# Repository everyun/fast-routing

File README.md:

# Fast-Routing

A Rust port of [Freerouting](https://github.com/freerouting/freerouting) for
headless CLI (`fr-cli`) and native GPUI interactive (`fr-gui`) PCB
autorouting. The goal is capability parity with the released Freerouting
**2.3.0** jar, then decisively faster wall-clock and lower memory on modern
CPUs. No GPU compute required for routing.

## Acknowledgements & Tribute to Freerouting

`fast-routing` stands on the shoulders of giants. We express our deepest
respect and gratitude to **Alfons Wirtz**, the original creator of Freerouting,
as well as the **Freerouting Open Source Community and Maintainers** who have
nurtured and preserved this essential EDA project for over two decades.

Freerouting's mathematical foundations—such as exact 45° planar integer
geometry, Minimum Area Tree spatial bounding hierarchies, Bowyer-Watson
Delaunay ratsnest generation, and symmetric clearance matrix rules—remain a
masterclass in EDA algorithms.

`fast-routing` pays tribute to this legacy by re-implementing those geometric
principles in Rust.

## The reference

The reference is the released artifact, not a source tree:

- jar: `freerouting-2.3.0.jar` (Build-Revision `2d4de019`)
- router core in that jar is the **v19** algorithm
- IO / DRC / scoring packages in that jar are the **v2** code

See `docs/ARCHITECTURE.md` for the hybrid, `docs/ROADMAP.md` for gates, and
`docs/PARITY-DIVERGENCES.md` for declared differences.

## Installation

### Pre-built binaries

Pre-built binaries and SHA256 checksums are available on the [Releases](https://github.com/everyun/fast-routing/releases) page for:
- **macOS** Apple Silicon (`aarch64-apple-darwin`) & Intel (`x86_64-apple-darwin`)
- **Linux** x86_64 (`x86_64-unknown-linux-gnu`) & ARM64 (`aarch64-unknown-linux-gnu`)
- **Windows** x86_64 (`x86_64-pc-windows-msvc`)

Download and extract the archive for your system, then place `fr-cli` (or `fr-cli.exe` on Windows) in your `PATH`.

### From source (Cargo)

With a Rust 1.75+ toolchain installed:

```bash
# Clone the repository
git clone https://github.com/everyun/fast-routing.git
cd fast-routing

# Install fr-cli into ~/.cargo/bin
cargo install --path crates/fr-cli
```

Or build both CLI and GUI locally without installing:

```bash
cargo build --release -p fr-cli -p fr-gui
# Executables are at target/release/fr-cli and target/release/fr-gui
```

Verify the installation:

```bash
fr-cli --version
```

## Quick start

```bash
# Build the CLI and GPUI GUI
cargo build --release -p fr-cli -p fr-gui

# Autoroute a Specctra .dsn file headlessly
target/release/fr-cli -de path/to/board.dsn -do path/to/output.ses -mp 5

# Open an interactive board viewer / router GUI
target/release/fr-gui --open path/to/board.dsn

# Render a headless board snapshot from the GUI pipeline (<50 MB RSS)
target/release/fr-gui --open path/to/board.dsn --screenshot board.png
```

Flags, Java compatibility, and our extras (`--threads`, `--portfolio`,
`--no-optimizer`, …) are in `docs/CLI.md`. Router knobs are in
`docs/SETTINGS.md`.

## How to evaluate

Quality and time are judged by the referee harness, not by self-reports.

```bash
bench/fetch_fixtures.sh
cargo build --release -p fr-cli
python3 bench/run_bench.py
```

Details, judging rules, and fixture classification: `bench/README.md`.

## Measured results

Headline numbers measured **serially on a quiet machine** (Apple M3 Ultra, 2026-11-19,
commit `99b2ce4`, W=1, `nice -n 10`, J/R interleaved per board, `-mp 20 --timeout 300`)
against a **clean Java reference**: Freerouting 2.3.0 jar (`freerouting-2.3.0.jar`, Build-Revision
`2d4de019`, OpenJDK 26.0.2), run headlessly with fanout + optimizer enabled and a fresh empty
`--user_data_path` for every invocation (hermetic — the shared `$TMPDIR/freerouting/freerouting.json`
is a known measurement contaminant). Quality is judged by the independent referee harness
(`bench/tools/g21_referee` + `g21_judge.py`), never by self-reports. Provenance:
`bench/results/ledger4/20261119-99b2ce4/` (per-board rows in the report tables there).

| metric | value |
|---|---|
| wall-clock geomean, 26 unique `java_finished` designs | **13.84×** vs Java (in-tool geomean **7.86×**; **26 / 26 wins**) |
| wall-clock geomean, all 27 `java_finished` boards | **12.89×** (in-tool **7.47×**; **27 / 27 wins — 0 losses**) |
| total wall-clock, 26 unique designs | Java 753.1 s vs Rust **259.7 s** (**2.90×**); total in-tool 707.0 s vs **259.5 s** (**2.72×**) |
| total wall-clock, all 27 boards | Java 814.7 s vs Rust **290.0 s** (**2.81×**); total in-tool 766.0 s vs **289.8 s** (**2.64×**) |
| peak RSS, 26 unique designs (all 27 boards) | Java 4 846.4 MB vs Rust **82.9 MB** (~58.5× lower); all 27: Java 4 923.6 MB vs Rust **89.3 MB** (~55.1× lower; worst-case 6 955.5 MB vs 565.0 MB, ~12.3×) |
| added violations (judged − unmodified import) | **0** across all 27 `ledger4` boards, all 45/45 judgeable mainline boards, and all 9/9 OOS boards |
| 46-board mainline quality suite (`gate4`, salmon, `99b2ce4`) | **46 / 46 PASS** (`0` added violations across 45/45 judgeable boards); comparative vs Java: **26 / 26 PASS (12 win / 14 tie / 0 loss)**; OOS **9 / 9 PASS** (`bench/results/gate4-quality/20261119-99b2ce4/`) |
| angle violations generated by the router | **0** across all 33 G4-evaluated boards (24 mainline + 9 OOS, `bench/results/g4-gate/99b2ce4/`) |
| KiCad 10.0.5 import | all 8 `.kicad_pcb` out-of-sample boards import cleanly with zero errors and `unconnΔ <= 0` (`bench/results/g4-gate/99b2ce4/`) |

### Former quality & wall-clock gaps closed (`ledger3` → `ledger4`)

Every former quality and speed loss from the `ledger3` (`9b08338`) baseline is resolved in `ledger4` (`99b2ce4`), with **0 quality losses and 0 wall-clock/in-tool losses across all 27 `java_finished` boards**:

| board | Java (ledger4) | Rust ledger3 (`9b08338`) | Rust ledger4 (`99b2ce4`) | wall J/R (ledger4) |
|---|---|---|---|---|
| `Issue039-bug-design` | 179.22 s (`10u / 25v`) | 284.34 s (`30u / 25v`) | **130.84 s** (`4u / 25v`) | **1.37×** (better quality & faster) |
| `Issue102-Mars-64-revE-rot00` | 85.43 s (`0u / 64v`) | 126.38 s (`1u / 64v`) | **38.69 s** (`0u / 64v`) | **2.21×** (0u tie & faster) |
| `Issue110-Pajalnaja_stancija` | 61.52 s (`6u / 18v`) | 97.89 s (`6u / 18v`) | **30.23 s** (`6u / 18v`) | **2.03×** (6u tie & faster) |
| `Issue110-RelayModule` | 9.32 s (`0u / 4v`) | 15.50 s (`0u / 2v`) | **4.05 s** (`0u / 2v`) | **2.30×** (fewer violations & faster) |

Full per-board table (all 27 boards, both tools, RSS, and historical `r1`/`r2`/`r3` comparisons): [`bench/results/ledger4/20261119-99b2ce4/report.md`](bench/results/ledger4/20261119-99b2ce4/report.md).

### Architectural optimization & post-9b08338 changes

The `ledger4` (`99b2ce4`) gains build on exact geometric fast paths with **zero algorithmic divergence** (8/8 deterministic SHA-256 baseline match) plus converged via optimization:

- **Exact $\mathbb{R}^2$ `OctR2` Fourier-Motzkin overlap & cached tree hulls**: replaces hot-loop `Simplex::enlarge`, `remove_redundant_from_sorted`, `board_bounds` scans, and SAT fallback on 45°/90° geometry in pull-tight, shove, and room completion with stack-allocated `i64` intervals while matching exact simplex semantics bit-for-bit.
- **Stack `FastPoint` & cached `CompletedShape::oct_r2`**: eliminates `BigInt` heap allocations on `restrain_shape` corner/segment intersections and room overlap tests.
- **Deflected neckdown angle-knee guard (`insert_angle_compliant_neckdown_segment`)**: bridges off-axis `spring_over`/`pull_tight` neckdown stubs via `calculate_additional_corner`, bringing router-generated G4 angle violations to **0 / 33 boards** (including `cla45-sensor-l6`).
- **`RouterObserver`, fast board snapshot, and native GPUI GUI (`crates/fr-gui`)**: live routing canvas, layer switcher, ratsnest inspector, and headless `--screenshot` renderer (<50 MB RSS).

Previously landed convergence changes (provenance: `bench/results/main-sweeps/`, `bench/results/ledger4/20261119-99b2ce4/`):

- **Fallback-via clearance-class fix + board-via fallback default-off** (`d8cc31c`, `3bb7576`):
  the fallback via uses the net's via clearance class (DSN net-class semantics, zero added
  violations), and board-level via fallback ships disabled by default per the tree-desync
  ruling (upstream's fallback is self-consistently wrong: `RoutingBoard.java:1019-1035` assigns
  the default class on read-back; `DECISIONS.md` 2026-09-07 01:00/01:40). Accepted cost:
  Issue039 default mode **30 → ~36u**; re-decided when Full becomes default.
- **Fanout stop rules aligned upstream** (`007d0bb`, `c94876d`): our fanout no-progress stop was
  removed (the "doesn't lose coverage" argument was falsified by the RelayModule trace),
  restoring upstream's three stop rules. Win: **Issue219 361 → 299u**; accepted costs:
  sensor-l6 110 → 119u, power-io 60 → 74u (`DECISIONS.md` 2026-09-07 03:25).
- **Issue039 under a job deadline — measured, not the same as budgetless quality.** Serial
  salmon, `-mp 20 --job-timeout 285`, default mode (integrator's merge records,
  `REPORT-integrate.md`): `9b08338` ≈ **30u/25v** → current mainline (`ece1508`) **40u/25v**.
  Cause: with the no-progress stop removed, fanout escapes more pins (606 → 729) and takes
  longer, so only 6 passes finish before the deadline — a **budget-allocation problem, not a
  search regression**: without a deadline, deterministic 20-pass runs on the current mainline
  are **4u better** than `9b08338`. Landed (`2a26e1a`): the fanout stage's share of the job
  budget is capped at **25%** (`FR_FANOUT_BUDGET_PCT` overrides; no deadline — no cap, and
  no-deadline deterministic runs stay byte-identical).
- **FANOUT_VIA predicate kept as the stricter own version** (revert of the upstream
  `is_fanout_via` port, `PARITY-DIVERGENCES.md`): a declared intentional divergence that holds
  **Issue102 at 1u** (the upstream predicate had regressed it to 13u in the orca sweep through
  slower convergence; `DECISIONS.md` 2026-09-07 05:35/06:35).
- **45° family tree keeps trace/outline strips at their base Simplex** (`d89ded9`): recorded in
  `docs/PARITY-DIVERGENCES.md`; Issue054 stays at **4.7 s / 0u**.
- **OptViaAlgo via location optimization during pull-tight** (`767283d`, `fdc0259`): ported
  upstream's `OptViaAlgo` (`REPORT-optvia.md`, `DECISIONS.md` 2026-09-08 20:20). Win:
  **Issue039 deterministic 20-pass converges to 4u/25v** (Java reference: 10u), and 285s deadline
  improves to **24u** (from 39u); `cla45-power-io-l6` 285s improves to **64u** (from 74u);
  `cla45-sensor-l6` improves to **113u** (from 115u). Accepted costs: `kicad-coldfire-unrouted`
  285s 9u → 19u (opt-via work makes passes slightly more expensive, finishing fewer passes before
  cutoff), `easyeda-pcb1` 8u → 9u, and `Issue102` under Full mode 285s 0u → 1u (serial det stays
  **0u board complete**); Doors 285 s Issue102 0u → 2u (det still 0u at pass 17 vs 11; fix in
  progress, TASK-102-deadline).

### Parallel routing

`--parallel-connections` defaults to **1**: it is the only mode that is bit-for-bit deterministic
and referee-clean everywhere. Measured applicability of `--parallel-connections 8`
(REPORT-t3, orca): **2.3–3.1× route-stage speedup on sparse large boards**
(Issue230, Issue157, Issue269), with 24-board + 9-OOS acceptance PASS (0 worse, 0 added
violations) — but on pin-dense congested boards corridor pre-emption makes parallel search
unequal to serial greedy allocation and can break convergence, so the default stays 1.

The 45° router mode is a **runtime** choice via the environment variable `FR_ROUTER_TILING_45=doors|full|off` (default `doors`): the `full` value selects the
unified full-tiling chain, which matches Java's per-expansion cost on the hardest boards
(Issue039 ~35.7 µs/exp ≈ Java 36) and wins on multi-layer boards under budget
(sensor-l6 119u vs Doors 123u), but still regresses a few congested boards
(e.g. RelayModule 0→2u), so **Doors remains the default** until it is zero-regression
(`docs/PARITY-DIVERGENCES.md`, REPORT-tiling45-default.md).

### How to reproduce

```bash
# 1. Build release binaries
cargo build --release -p fr-cli -p g21-referee

# 2. Serial ledger (quiet machine required; numbers above are W=1, nice -n 10)
python3 bench/run_bench.py --serial-perf --passes 20 --timeout 300 --concurrency 1

# 3. One-touch quality acceptance vs the recorded mainline sweep
#    (runs remotely on orca/salmon/whale, auto-picks the least loaded host,
#     compares same-doors-mode against bench/results/main-sweeps/)
bench/tools/remote/accept.sh <worktree-or-commit> --suite 24+oos --doors default
```

Remote test machines (quality sweeps only; serial timings are always taken on a quiet Mac):
- **orca** — 80-core Debian 13
- **salmon** — EPYC 32c/64t (fastest single-core, use for deadline-sensitive suites)
- **whale** — old Xeon, non-deadline boards and byte-identity checks only

Addresses are in the local ops notes.

## License

This project is licensed under the [GNU General Public License v3.0
(GPL-3.0)](LICENSE) in alignment with upstream Freerouting.

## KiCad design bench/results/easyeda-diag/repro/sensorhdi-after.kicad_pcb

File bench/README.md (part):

# bench/ — Freerouting (Java) vs fr-cli (Rust) benchmark harness

This is the project's referee: a head-to-head comparison of the reference
Java Freerouting against our Rust `fr-cli` over the upstream fixture suite.
Every future optimization gets judged by it. Python 3, stdlib only.

| file | role |
|---|---|
| `manifest.py` → `fixtures-manifest.json` | what each fixture *is*: md5 dedup, coverage properties, Java classification, 3-run stability |
| `reference.json` | pinned release jar (filename, sha256, build revision, published date, URL) |
| `restore_reference.sh` | idempotent restore of jar + release source + 46 fixtures into `~/fr-ref`, `/tmp` symlinks only |
| `run_bench.py` | runs both tools, classifies every row from the manifest, writes `results.json` + `report.md` |
| `run_java_stability.py` | 3-run Java stability sweep (`-mp 20`, 300 s, W=4) with a hermetic `--user_data_path` per call |
| `check_ses.py` | independent (coarse) DSN/SES checker — totals **and per-net** wire length / via count |
| `tools/g21_referee/` | the real referee: `(dsn, ses)` in, one JSON verdict out, same binary for both tools |
| `tools/g21_judge.py` | the ROADMAP G2.1 gate — see "Judging a session" below |
| `test_bench.py`, `tools/tests/`, `analysis/test_campaign.py` | self-tests; hermetic, no fixtures or jar needed |

## Quick start

```sh
# 0. Restore the pinned Java reference (jar, 2.3.0 source, 46 fixtures)
#    Real files: ~/fr-ref/{frbase,fr-java-release,freerouting-upstream}
#    Symlinks:   /tmp/frbase, /tmp/fr-java-release, /tmp/freerouting-upstream
bash bench/restore_reference.sh

# 1. Build our CLI
cargo build --release -p fr-cli

# 2. Generate the fixture manifest (row classification + the geomean need it)
python3 bench/manifest.py

# 3. Run the full top-level suite (46 fixtures x 2 tools, 20 passes, 300s timeout each)
python3 bench/run_bench.py

# Smoke subset / variations
python3 bench/run_bench.py --fixtures 'Issue026*' --fixtures 'Issue143*'
python3 bench/run_bench.py --only-rust --passes 5
python3 bench/run_bench.py --jar /tmp/fr-lab-release/freerouting-lab.jar \
    --passes 9999 --timeout 600 --config mp9999-lab

# Re-render an old run's report with today's report code (runs nothing)
python3 bench/run_bench.py --render-from bench/results/<stamp> --report-out -

# 4. Judge the run against ROADMAP G2.1 (see "Judging a session")
cargo build --release -p g21-referee
python3 bench/tools/g21_judge.py --ours bench/results/<stamp>/ses

# Harness self-tests (fast, hermetic) and manifest staleness check
python3 bench/test_bench.py
python3 -m unittest discover -s bench/tools/tests
python3 bench/analysis/test_campaign.py
python3 bench/manifest.py --check
```

Results land in `bench/results/<timestamp>/`:

- `results.json` — `{"meta": {...}, "records": [...]}`, written incrementally
  so a partial/aborted suite still leaves data. `meta` pins the run's config
  (`config_label`, jar, passes, timeout, manifest, quality predicate, repo
  rev) so two runs made under different reference configs are never silently
  compared. Readers accept the older bare-list form too.
- `report.md` — comparison table + summary (per-row class, quality verdict,
  quality-filtered geomean)
- `logs/` — raw stdout/stderr per run (includes the `/usr/bin/time -l` footer)
- `ses/` — the produced `.ses` session files
- `nets/<fixture>.<tool>.nets.json` — the per-net breakdown from `check_ses.py`
  (kept out of `results.json`, which would otherwise be mostly net names)

Defaults (all overridable): fixtures `/tmp/freerouting-upstream/fixtures/*.dsn`
(top level only), Java `/opt/homebrew/opt/openjdk/bin/java`, jar
`/tmp/frbase/freerouting-2.3.0.jar` (sha256 pinned in `bench/reference.json`;
`run_bench.py` refuses a mismatch unless `--allow-unpinned-jar`), Rust binary
`target/release/fr-cli`, manifest `bench/fixtures-manifest.json`.

Every Java invocation creates a fresh empty directory and passes
`--user_data_path=` pointing at it. Without that flag the release jar reads
`$TMPDIR/freerouting/freerouting.json`, and that file has been observed to
turn `router.fanout.enabled` / `router.optimizer.enabled` off; `-de` only
restores `router.enabled`. See docs/PARITY-DIVERGENCES.md (Optimizer). Each
results.json Java record stores the effective
`router.enabled / fanout.enabled / optimizer.enabled / max_passes` under
`java_settings` (inferred from the stage log lines, because the jar does not
print the resolved booleans at INFO).

## Fixture manifest (`manifest.py` → `fixtures-manifest.json`)

The manifest answers three questions per board, so that neither the harness
nor a reader has to guess them.

**1. Is this the same design as another fixture?** `dedup` groups fixtures by
exact md5; `variant_family` is a *curated* table (`VARIANT_FAMILIES` in
`manifest.py`) of same-design variants. Adding fixtures means revisiting that
table — it is provenance, not something derived from the bytes.

```
46 files → 45 distinct md5 → 39 independent designs
```

The one byte-identical pair is `Issue110-Pajalnaja_stancija.dsn` /
`Issue110-Паяльная станция.dsn` (the same upstream attachment uploaded twice,
once transliterated). `run_bench.py` counts an md5 group **once** in the
filtered aggregate; the duplicate row is still shown, marked
`byte-identical duplicate of <first member present in the run>`.

**2. What does the board exercise?** Parsed from the DSN with `check_ses.py`'s
tolerant reader: `signal_layers`, `plane_layers` (`(type power)`),
`snap_angle_declared`, `host_cad`/`host_version`, `has_autoroute_settings`,
`has_class_class`, `has_preexisting_wiring` / `has_preexisting_copper` (+ wire
and via counts inside the `(wiring …)` scope), `nets_total` /
`nets_multi_pin`, `components_placed`.
Current suite (the manifest's `coverage` block; reproduce with
`python3 bench/manifest.py`):

| property | value |
|---|---|
| layers | 40 boards 2-layer, 5 boards 4-layer, 1 with no layers at all |
| power planes | 3 boards (Issue145, Issue230, Issue269) |
| `snap_angle` declared | 2 boards, both `fortyfive_degree` — **nothing exercises 90° or none** |
| `host_cad` | 41 KiCad, 2 CadSoft, 3 absent |
| `autoroute_settings` in the DSN | 2 boards |
| `class_class` rules | 0 boards |
| pre-existing wiring | 23 boards have `(wire …)` in the `(wiring …)` scope; 26 have wires **or** pre-placed vias (Issue145 ships 42 vias and no traces) |
| not a Specctra DSN at all | 1 (`Issue006-LPC18XX_43XX_SCH.dsn`, a binary OLE compound document renamed `.dsn`) |

That table is the argument for the mandatory out-of-sample tier in ROADMAP
G2.4: the upstream suite is a 2-layer KiCad monoculture.

**3. What did Java do with it?** `java.class`, read off a real bench run
(`--results`, default `bench/results/java-reference/results.json` — round 1 of
the hermetic stability sweep):

| class | rule |
|---|---|
| `java_timeout` | killed at the run's timeout |
| `java_crash` | signal / unexpected exit code / no parseable completion line |
| `java_degenerate` | finished, but with final score `0.00` **or** 0 multi-pin nets parsed from the DSN — Java never had anything to route (`Issue006`, `Issue229`) |
| `java_finished` | everything else |
| `java_unknown` | fixture absent from the source results (or no manifest loaded) |

On the hermetic `-mp 20` / 300 s re-baseline checked in at
`bench/results/java-reference/` (2026-09-04, `--user_data_path` isolated):
27 `java_finished`, 17 `java_timeout`, 1 `java_crash`, 1 `java_degenerate`.
The pre-isolation baseline (`bench/results/20260828-013025`, 29/14/1/2) was
measured with fanout/optimizer disabled by a leaked `$TMPDIR` freerouting.json;
it is archived at `bench/results/java-reference-contaminated-20260829/` and
`bench/compare_java_reference.py` prints the per-board old-vs-new table.
**Regenerate the manifest after the `-mp 9999` re-baseline (ROADMAP M0.5)** or
the classes describe a config nobody runs any more. `manifest.py --check`
exits 1 when the checked-in manifest differs from a fresh generation (CI).

**4. Does Java give the same answer twice?** `stability`, folded in from
`bench/results/java-stability/<stem>.r{1,2,3}.log` — three runs of the capped
baseline's exact command line. `stability.class` is what G2.1 reads:

| class | rule | what the gate does with it |
|---|---|---|
| `stable` | ≥2 runs reached a final score and all of them report the same `(unrouted, violations)` | the only class that unlocks the comparative gate |
| `unstable` | ≥2 runs reached one and they disagree (including "sometimes finishes inside the cap, sometimes not") | absolute gate, exactly like a timeout |
| `no_result` | the runs agree there is nothing to report: killed at the cap, or not a routable board | absolute gate |
| `unmeasured` | fewer than two runs on disk — the sweep has not covered this fixture | absolute gate |

`stability.unrouted` / `violations` / `started_unrouted` are **Java's own**
numbers and are comparable only with each other, never with a referee count:
they are what "did the reference make progress on this board?" is answered
with (see the anti-degeneracy guard below).

The logs are gitignored like every other `bench/results/**/*.log`, so
`manifest.py --check` compares on a projection that drops the `stability`
block when they are absent, the same trick it already uses for `uncapped`.

## Judging a session (ROADMAP G2.1)

This is the normative description of the gate. `bench/tools/g21_judge.py`
implements it and `bench/tools/g21_referee/` measures it; changing one without
the others is a bug.

```sh
cargo build --release -p g21-referee
python3 bench/tools/g21_judge.py --ours <dir-of-*.rust.ses> \
    [--java <dir-of-*.java.ses>] [--sweep <our-runner's sweep.json>]
```

### The overlay: which board a session is read into

`read_session` **merges** into the board it is handed, and both tools re-emit
the input board's copper in their session. Reading a session into the full DSN
import therefore inserts every pre-existing trace twice — on `Issue093` that
alone takes the judged violation count from 192 to 322. The session is read
into `fr_io::specctra::strip_session_copper(dsn)` instead: the same DSN with
exactly the copper a session carries removed.

"Exactly" is load-bearing, and emptying the whole `(wiring …)` scope is *not*
it. `SesWriter.writeNet` skips `SYSTEM_FIXED` items, which is what `(type fix)`
copper imports as, so that copper is on the board and in no session file.
`Issue230-CNH_Functional_Tester_1.dsn` is the suite's only board with any (8
wires), and emptying the scope mis-judges it in both directions at once:

| Issue230, same session | unrouted | violations |
|---|---|---|
| our routed board, in process | 5 | 16 |
| judged into an emptied `(wiring)` | 8 | **14** |
| judged into `strip_session_copper` | 5 | 16 |

Three connections lost *and* two clearance violations forgiven. The reference's
own session for that board reads 2/16 through the correct overlay and 8/14
through the emptied one, so the error is not even symmetric between tools.

The **baseline** (`g21-referee <dsn>` with no session) is the *unmodified*
import: `added = judged − baseline` only means anything if the baseline is the
board as delivered.

A violation whose two items are both `USER_FIXED` is never charged to either
tool — it is a property of the input board.

### The two gates

A board is judged **comparatively** only when the reference's answer is a fact
that reproduces: `java.class == java_finished` **and**
`stability.class == stable` **and** a reference session exists.

```
comparative:  added_violations(ours) <= added_violations(java)
         AND  unrouted(ours)         <= unrouted(java)
```

Everything else — timeout, crash, degenerate, unstable, unmeasured, or a
missing reference session — is judged **absolutely**:

```
absolute:  added_violations(ours) == 0
      AND  unrouted(ours) <= unrouted(input)
      AND  (no reference session OR unrouted(ours) <= unrouted(java))
      AND  the anti-degeneracy guard
```

Both gates additionally require `ses_errors == 0`: a session the reader has to
guess at is not a result, however good its numbers look.

### The anti-degeneracy guard

`unrouted <= input` on its own would let "emit an empty session" pass every
absolute board. It cannot, because a board may only stand still when *the
reference implementation could not move it either*. Progress is a recorded
property of the reference — from the manifest, never from the run being
judged — and is looked for in this order:

1. a referee-judged reference session that beats the input;
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
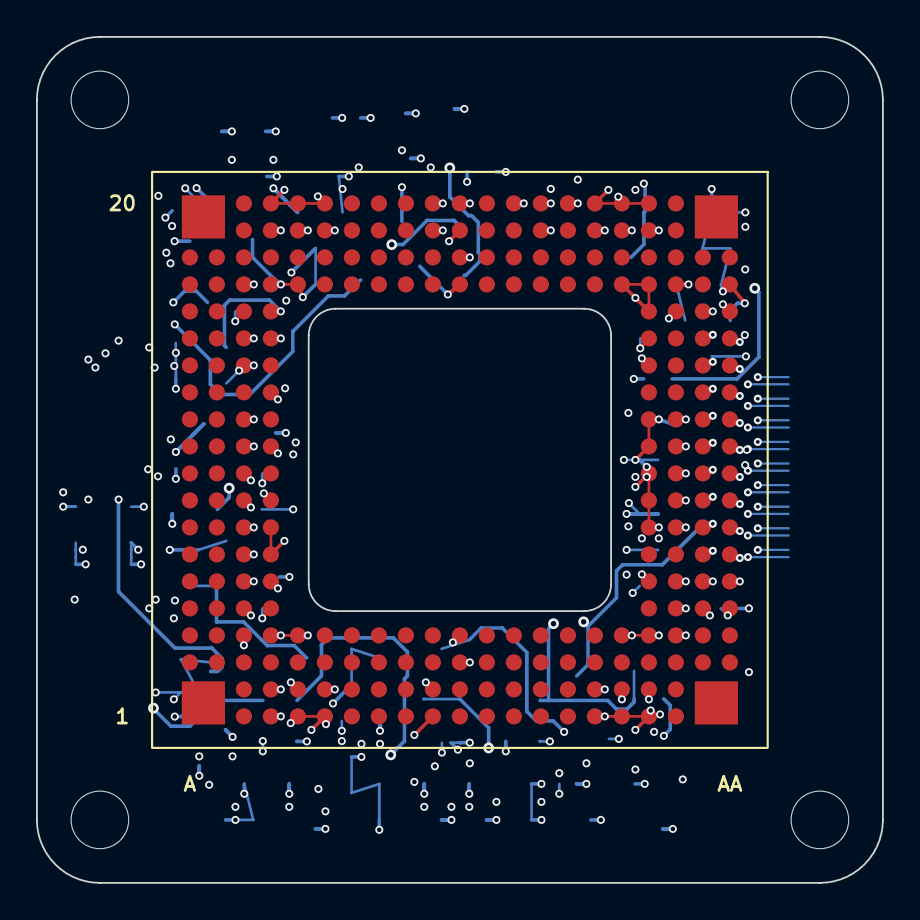
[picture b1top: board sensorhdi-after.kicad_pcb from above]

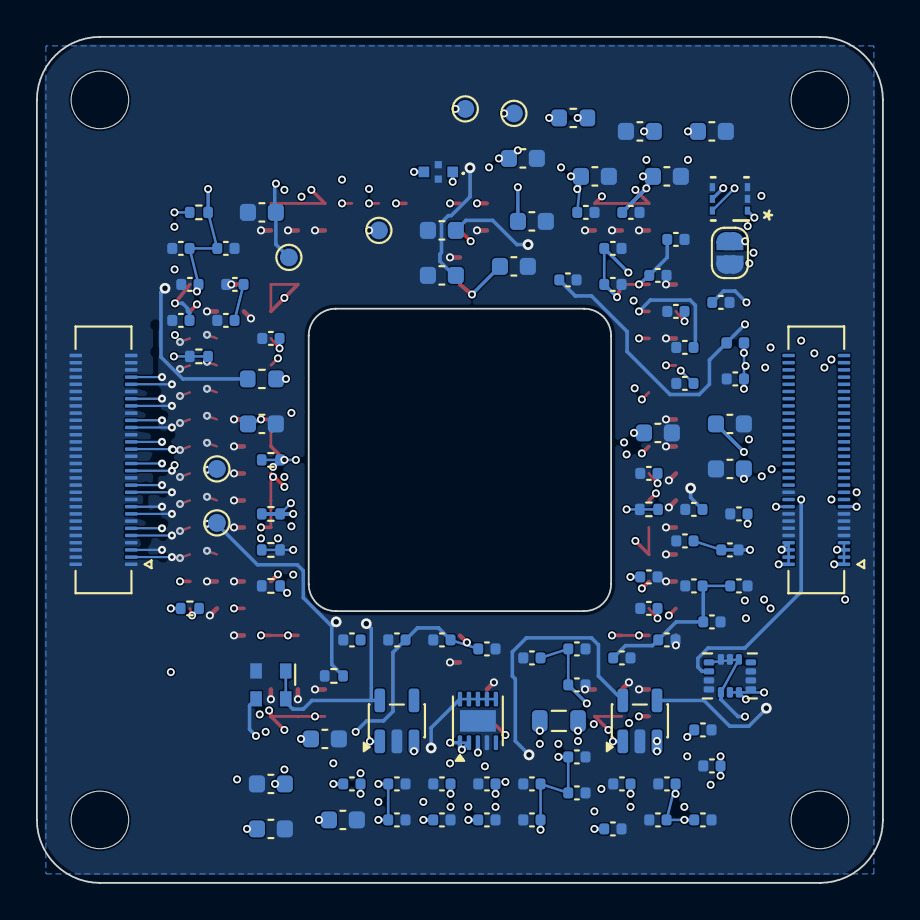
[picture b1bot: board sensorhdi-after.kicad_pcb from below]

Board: 6 copper layers, 47.0 x 47.0 mm, 108 parts (103 on the bottom side), 51 nets.

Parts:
C1, C3, C4, C6, C8, C17, C18, C24, C27, C28, C29, C34, C36, C38, C43, C47, C50, C52, C53, C58, C61, C62, C67, C75: 1uF; C_0402_1005Metric
C2, C9, C16, C22, C23, C31, C33, C41, C45, C46, C49, C54, C55, C56, C57, C59, C63, C64, C65, C66, C70, C71, C72, C73: 100nF; C_0402_1005Metric
C5, C7: 2.2uF; C_0603_1608Metric
C10, C13, C15, C19, C21, C25, C26, C32, C35, C37, C39, C44, C48: 4.7uF; C_0603_1608Metric
C11: NFM18CC101R1C3D
C12: 22uF; C_0603_1608Metric
C14, C69: 10uF; C_0603_1608Metric
C20, C30, C40, C42, C51, C60: 1000pF; C_0402_1005Metric
C68, C74: 10nF; C_0402_1005Metric
CN1, CN2: DF40C-60DS-0.4V; Hirose_DF40C-60DS-0.4V
FB1, FB3: BLM18KG102SN1D; L_0603_1608Metric
FB2: BLM15AX300SN1D; L_0402_1005Metric
H1, H2, H3, H4: MountingHole; MountingHole_3.2mm_M3
JP1: SolderJumper_2_Open; SolderJumper-2_P1.3mm_Open_RoundedPad1.0x1.5mm
L1: DFE201210U-2R2M=P2; L_0805_2012Metric
R1, R2: 47K; R_0402_1005Metric
R3, R4, R8, R10: 10K; R_0402_1005Metric
R5: 22R; R_0402_1005Metric
R11: 3.01K; R_0402_1005Metric
R12: 1.15K; R_0402_1005Metric
TP1, TP2, TP3, TP4, TP9, TP10: TestPoint; TestPoint_Pad_D1.0mm
U1: AP3418KTR-G1; SOT-23-5
U2: IMX294
U3: LP5907MFX-1.8; SOT-23-5
U4: TPS7A90; Texas_S-PDSO-N10_EP1.2x2mm
U5: ECS-2520MV-240-DN-TR; Oscillator_SMD_Abracon_ASDMB-4Pin_2.5x2.0mm
U6: TMP117AIDRVR
U8: ICM-42688-P; PQFN50P300X250X97-14N

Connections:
+1V2: C12.2, C17.2, C18.2, C20.2, C21.2, C22.1, C23.1, C24.1, C26.2, C27.2, C29.2, C30.2, C31.1, C33.1, C34.1, C35.2, C38.2, C39.2, C40.2, C41.1, C42.2, C43.1, C46.1, C47.2, C49.1, C50.2, C51.2, C52.2, C53.2, C55.1, C56.1, C58.2, C60.2, C61.2, C62.2, C63.1, C64.1, L1.2, R3.1, TP1.1, U2.AA6, U2.AA16, U2.D1, U2.D20, U2.E1, U2.E20, U2.F1, U2.F20, U2.K1, U2.K20, U2.T1, U2.T20, U2.U1, U2.U20, U2.V1, U2.V6, U2.V8, U2.V9, U2.V10, U2.V11, U2.V12, U2.V20
+1V8: C13.1, C16.1, C54.2, C71.1, C73.1, C74.1, C75.1, R8.1, TP2.1, U2.AA17, U2.D6, U2.D15, U2.L19, U3.5, U5.1, U5.4, U6.5 (V+), U8.5 (VDDIO), U8.8 (VDD), U8.12 (AP_CS)
+2V9: C19.2, C25.2, C28.2, C32.2, C36.2, C37.2, C44.2, C45.2, C48.2, C57.2, C59.2, C65.2, C66.2, C68.2, C69.1, R11.2, TP3.1, U2.D4, U2.D7, U2.D8, U2.D17, U2.E4, U2.E17, U2.L4, U2.L17, U2.U4, U2.U17, U2.V4, U2.V16, U2.V17, U4.1, U4.2
+3V3: C11.1, C72.1, CN2.1, CN2.2, CN2.3, CN2.4, CN2.5, CN2.6, CN2.7, CN2.8, FB1.1, FB2.1, FB3.2, TP4.1
CAM_CLK_N: CN1.17, U2.Y9
CAM_CLK_P: CN1.15, U2.AA9
CAM_D0_N: CN1.11, U2.Y8
CAM_D0_P: CN1.9, U2.AA8
CAM_D1_N: CN1.23, U2.Y10
CAM_D1_P: CN1.21, U2.AA10
CAM_D2_N: CN1.5, U2.Y7
CAM_D2_P: CN1.3, U2.AA7
CAM_D3_N: CN1.29, U2.Y11
CAM_D3_P: CN1.27, U2.AA11
CAM_EN: R10.1, TP9.1, U1.1, U3.3, U4.7
CLOCK: R5.1, U2.AA5
GND: C1.2, C2.2, C3.2, C4.2, C5.2, C6.2, C7.2, C8.2, C9.2, C10.1, C11.2, C12.1, C13.2, C14.2, C15.2, C16.2, C17.1, C18.1, C19.1, C20.1, C21.1, C22.2, C23.2, C24.2, C25.1, C26.1, C27.1, C28.1, C29.1, C30.1, C31.2, C32.1, C33.2, C34.2, C35.1, C36.1, C37.1, C38.1, C39.1, C40.1, C41.2, C42.1, C43.2, C44.1, C45.1, C46.2, C47.1, C48.1, C49.2, C50.1, C51.1, C52.1, C53.1, C54.1, C55.2, C56.2, C57.1, C58.1, C59.1, C60.1, C61.1, C62.1, C63.2, C64.2, C65.1, C66.1, C67.2, C69.2, C70.1, C71.2, C72.2, C73.2, C74.2, C75.2, CN1.1, CN1.2, CN1.4, CN1.6, CN1.7, CN1.8, CN1.10, CN1.12, CN1.13, CN1.14, CN1.16, CN1.18, CN1.19, CN1.20, CN1.22, CN1.24, CN1.25, CN1.26, CN1.28, CN1.30, CN1.31, CN1.32, CN1.34, CN1.36, CN1.37, CN1.38, CN1.40, CN1.42, CN1.43, CN1.44, CN1.46, CN1.48, CN1.49, CN1.50, CN1.52, CN1.54, CN1.55, CN1.56, CN1.57, CN1.58, CN1.59, CN1.60, CN2.9, CN2.10, CN2.11, CN2.12, CN2.13, CN2.14, CN2.15, CN2.16, CN2.22, JP1.1, R1.2, R2.2, R4.2, R10.2, R12.1, U1.2, U2.C4, U2.C6, U2.C7, U2.C8, U2.C9, U2.C10, U2.C11, U2.C12, U2.C15, U2.C17, U2.D2, U2.D19, U2.E2, U2.E19, U2.F2, U2.F19, U2.K2, U2.K19, U2.L3, U2.L18, U2.T2, U2.T19, U2.U2, U2.U19, U2.V2, U2.V19, U2.W4, U2.W6, U2.W8, U2.W9, U2.W10, U2.W11, U2.W12, U2.W16, U2.W17, U2.Y5, U2.Y6, U2.Y16, U3.2, U4.4, U4.11, U5.2, U6.2 (GND), U6.3 (ALERT), U6.4 (ADD0), U8.1 (AP_SDO/AP_AD0), U8.2 (RESV_2), U8.3 (RESV_3), U8.6 (GND), U8.7 (RESV_7), U8.10 (RESV_10), U8.11 (RESV_11)
unnamed: C1.1, U2.C16
unnamed: C3.1, U2.D5
unnamed: C4.1, U2.D16
unnamed: C8.1, U2.C5
unnamed: JP1.2, U2.W5
unnamed: R3.2, R4.1, U1.5
unnamed: L1.1, U1.3
unnamed: C15.1, FB3.1, U1.4
unnamed: C2.1, U2.V15
unnamed: C9.1, U2.C14
unnamed: R2.1, U2.V14
unnamed: R1.1, U2.D13
unnamed: C6.1, U2.D10
unnamed: C7.1, U2.D11
unnamed: C5.1, U2.D9
unnamed: C10.2, FB1.2, U3.1
unnamed: C68.1, R11.1, R12.2, U4.3
unnamed: C67.1, U4.8
unnamed: C11.3, C14.1, U4.6, U4.9, U4.10
unnamed: R5.2, U5.3
unnamed: C70.2, FB2.2
RST_1V8: CN2.19, R8.2, TP10.1, U2.P19
SCL_1V8: CN2.17, U2.P20, U6.1 (SCL), U8.13 (AP_SCL/AP_SCLK)
SDA_1V8: CN2.18, U2.R20, U6.6 (SDA), U8.14 (AP_SDA/AP_SDIO/AP_SDI)
SLVSEC_D4_N: CN1.35, U2.Y12
SLVSEC_D4_P: CN1.33, U2.AA12
SLVSEC_D5_N: CN1.41, U2.Y13
SLVSEC_D5_P: CN1.39, U2.AA13
SLVSEC_D6_N: CN1.47, U2.Y14
SLVSEC_D6_P: CN1.45, U2.AA14
SLVSEC_D7_N: CN1.53, U2.Y15
SLVSEC_D7_P: CN1.51, U2.AA15
XHS: CN2.21, U2.N20
XVS: CN2.20, U2.L20, U8.9 (INT2/FSYNC/CLKIN)

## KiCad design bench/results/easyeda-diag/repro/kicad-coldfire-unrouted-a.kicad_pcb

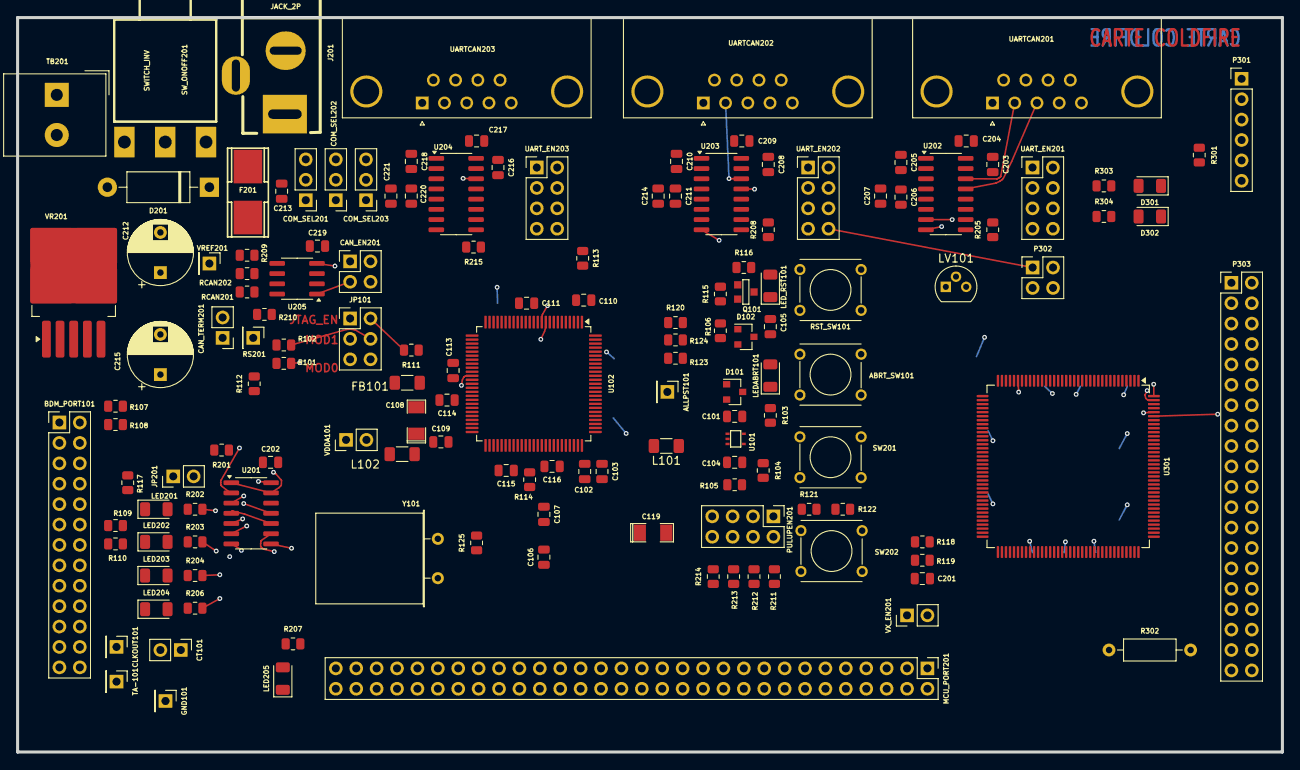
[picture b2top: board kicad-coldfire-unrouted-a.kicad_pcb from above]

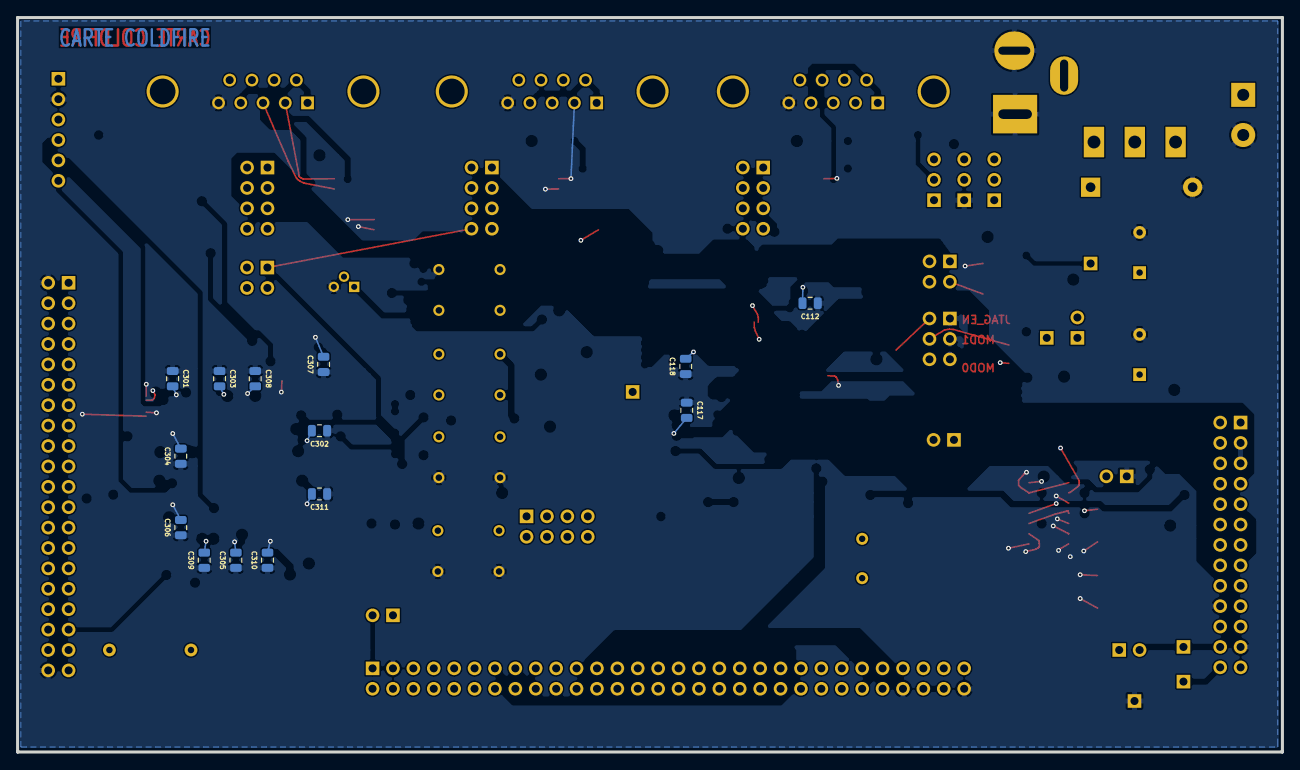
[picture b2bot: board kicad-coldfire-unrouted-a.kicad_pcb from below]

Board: 4 copper layers, 157.5 x 91.4 mm, 160 parts (14 on the bottom side), 209 nets.

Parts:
ABRT_SW101: SW_PUSH; SW_PUSH_SMALL
ALLPST101: CONN_1; PinHeader_1x01_P2.54mm_Vertical
BDM_PORT101: CONN_13X2; PinHeader_2x13_P2.54mm_Vertical
C101, C103, C104, C109, C110, C111, C112, C113, C114, C115, C116, C117, C118, C201, C202, C203, C204, C205, C206, C207, C208, C209, C210, C211, C213, C214, C216, C217, C218, C219, C220, C221, C301, C302, C303, C304, C305, C306, C307, C308, C309, C310, C311: 100nF; C_0805_2012Metric
C102, C105: 1nF; C_0805_2012Metric
C106, C107: 10pF; C_0805_2012Metric
C108: 10uF; SM1206POL
C119: 100uF; SM1206POL
C212: 10uF; CP_Radial_D8.0mm_P5.00mm
C215: 220uF; CP_Radial_D8.0mm_P5.00mm
CAN_EN201: CONN_2X2; PinHeader_2x02_P2.54mm_Vertical
CAN_TERM201: JUMPER; PinHeader_1x02_P2.54mm_Vertical
CLKOUT101: CONN_1; PinHeader_1x01_P2.54mm_Vertical
COM_SEL201, COM_SEL202, COM_SEL203: CONN_3; PinHeader_1x03_P2.54mm_Vertical
CT101: JUMPER; PinHeader_1x02_P2.54mm_Vertical
D101, D102: BAT54; D_SOT-23_ANK
D201: 1N4004; D_DO-15_P12.70mm_Horizontal
D301, D302: LED; LED_1206_3216Metric
F201: FUSE; FSUPCMS
FB101: BEAD; R_1206_3216Metric_Pad1.30x1.75mm_HandSolder
GND101: CONN_1; PinHeader_1x01_P2.54mm_Vertical
J201: JACK_2P; JACK_ALIM
JP101: JUMPER_TRIPLE; PinHeader_2x03_P2.54mm_Vertical
JP201: JUMPER; PinHeader_1x02_P2.54mm_Vertical
L101, L102: 10uH; R_1206_3216Metric_Pad1.30x1.75mm_HandSolder
LED201, LED202, LED203, LED204, LED205: LED; LED_1206_3216Metric
LEDABRT101: LED_RED; LED_1206_3216Metric
LED_RST101: LED_RED; LED_1206_3216Metric
LV101: DS1818; TO-92
MCU_PORT201: CONN_30X2; PinHeader_2x30_P2.54mm_Vertical
P301: CONN_6; PinHeader_1x06_P2.54mm_Vertical
P302: CONN_2X2; PinHeader_2x02_P2.54mm_Vertical
P303: CONN_20X2; PinHeader_2x20_P2.54mm_Vertical
PULUPEN201: CONN_4X2; PinHeader_2x04_P2.54mm_Vertical
Q101: 3906; SOT23EBC
R101, R102, R106, R107, R108, R109, R110, R111, R112, R211, R212, R213, R214: 4,7K; R_0805_2012Metric
R103, R116, R202, R203, R204, R206, R207: 270; R_0805_2012Metric
R104, R210, R303, R304: 1K; R_0805_2012Metric
R105: 20K; R_0805_2012Metric
R113: 0; R_0805_2012Metric
R114: 22; R_0805_2012Metric
R115: 4.7K; R_0805_2012Metric
R117, R118, R119, R120, R121, R122, R123, R124, R201, R205, R208, R215: 10K; R_0805_2012Metric
R125: 1M; R_0805_2012Metric
R209: 62; R_0805_2012Metric
R301: 4K7; R_0805_2012Metric
R302: 3,3; R_Axial_DIN0207_L6.3mm_D2.5mm_P10.16mm_Horizontal
RCAN201, RCAN202: R; R_0805_2012Metric
RS201: CONN_1; PinHeader_1x01_P2.54mm_Vertical
RST_SW101: SW_PUSH; SW_PUSH_SMALL
SW201, SW202: SW_PUSH; SW_PUSH_SMALL
SW_ONOFF201: SWITCH_INV; SW_SPDT
TA-101: CONN_1; PinHeader_1x01_P2.54mm_Vertical
TB201: CONN_2; Altech_AK300_1x02_P5.00mm_45-Degree
U101: 74AHC1G14; SOT353
U102: MCF5213-LQFP100; LQFP-100_14x14mm_P0.5mm
U201: 74HC125; SOIC-14_3.9x8.7mm_P1.27mm
U202, U203, U204: MAX202; SOIC-16_3.9x9.9mm_P1.27mm
U205: PCA82C251; SOIC-8_3.9x4.9mm_P1.27mm
U301: XCR3256-TQ144; TQFP-144_20x20mm_P0.5mm
UARTCAN201, UARTCAN202, UARTCAN203: DB9; DSUB-9_Female_Horizontal_P2.77x2.84mm_EdgePinOffset7.70mm_H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
UART_EN201, UART_EN202, UART_EN203: CONN_4X2; PinHeader_2x04_P2.54mm_Vertical
VDDA101: JUMPER; PinHeader_1x02_P2.54mm_Vertical
VR201: LT1129_QPACK; TO-263-5_TabPin3
VREF201: CONN_1; PinHeader_1x01_P2.54mm_Vertical
VX_EN201: JUMPER; PinHeader_1x02_P2.54mm_Vertical
Y101: 8MHz; Crystal_HC18-U_Horizontal

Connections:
+3.3V: ABRT_SW101.2, BDM_PORT101.9, BDM_PORT101.25 (P24), C101.2, C110.1, C111.1, C112.1, C113.1, C114.1, C115.1, C116.1, C117.1, C118.1, C119.1, C202.1, C203.1, C204.1, C208.1, C209.1, C215.1, C216.1, C217.1, C219.1, C301.1, C302.1, C303.1, C304.1, C305.1, C306.1, C307.1, C308.1, C309.1, C310.1, C311.1, L101.1, LEDABRT101.2 (A), LV101.2 (In), MCU_PORT201.59, P301.1, Q101.1 (E), R101.1, R102.1, R106.1, R107.1, R108.1, R109.1, R110.1, R111.1, R112.2, R118.2, R119.2, R120.2, R121.2, R122.2, R123.2, R124.2, R201.1, R207.2, R211.1, R212.1, R213.1, R214.1, R301.1, R302.1, RCAN202.1, U101.5 (VCC), U102.1 (VCC), U102.2 (VCC), U102.14 (VCC), U102.22 (VCC), U102.23 (VCC), U102.34 (VCC), U102.41 (VCC), U102.55 (VSTBY), U102.57 (VCC), U102.68 (VCC), U102.81 (VCC), U102.93 (VCC), U201.14 (VCC), U202.16 (VCC), U203.16 (VCC), U204.16 (VCC), U205.3 (VCC), U301.24 (VCC), U301.50 (VCC), U301.51 (VCC), U301.58 (VCC), U301.73 (VCC), U301.76 (VCC), U301.95 (VCC), U301.115 (VCC), U301.123 (VCC), U301.130 (VCC), U301.144 (VCC), VDDA101.1, VR201.1 (OUT), VR201.2 (SENSE), VX_EN201.1
/ALLPST: ALLPST101.1, U102.86 (ALLPST)
/AN0: MCU_PORT201.10, U102.43 (AN0/PAN0)
/AN1: MCU_PORT201.12, U102.44 (AN1/PAN1)
/AN2: MCU_PORT201.14, U102.45 (AN2/PAN2)
/AN3: MCU_PORT201.16, U102.46 (AN3/PAN3)
/AN4: MCU_PORT201.18, U102.54 (AN4/PAN4)
/AN5: MCU_PORT201.20, U102.53 (AN5/PAN5)
/AN6: MCU_PORT201.22, U102.52 (AN6/PAN6)
/AN7: MCU_PORT201.24, U102.51 (AN7/PAN7)
/BKPT-: BDM_PORT101.2, R107.2, U102.76 (~BKPT/TMS)
/CANRX: CAN_EN201.4, MCU_PORT201.28, PULUPEN201.7, U102.11 (SDA/CANRX/PAS1/URXD2)
/CANTX: CAN_EN201.1, MCU_PORT201.26, PULUPEN201.5, U102.10 (SCL/CANTX/PAS0/UTXD2)
/CLKIN/EXTAL: C107.1, R125.2, U102.73 (CLKIN/EXTAL), Y101.1
/CLKMOD0: JP101.6, R101.2, U102.40 (CLKMOD0)
/CLKMOD1: JP101.4, R102.2, U102.39 (CLKMOD1)
/DDAT0: BDM_PORT101.19, U102.77 (DDATA0/PDD4)
/DDAT1: BDM_PORT101.18, U102.78 (DDATA1/PDD5)
/DDAT2: BDM_PORT101.17, U102.83 (DDATA2/PDD6)
/DDAT3: BDM_PORT101.16, U102.84 (DDATA3/PDD7)
/DSCLK: BDM_PORT101.4, R108.2, U102.85 (DSCLK/~TRST)
/DSI: BDM_PORT101.8, R109.2, U102.79 (DSI/TDI)
/DSO: BDM_PORT101.10, R110.2, U102.80 (DSO/TDO)
/DSPI_DOUT: MCU_PORT201.17, U102.17 (QSPI_DOUT/EZPQ/CANTX/RXD0/PQS0), U301.47 (M12)
/DTIN0: MCU_PORT201.34, U102.36 (DTIN0/DTOUT0/PWM0/PTC0), U201.2 (D)
/DTIN1: MCU_PORT201.36, U102.37 (DTIN1/DTOUT1/PWM2/PTC1), U201.5 (D)
/DTIN2: MCU_PORT201.38, U102.31 (DTIN2/DTOUT2/PWM4/PTC2), U201.12 (D)
/DTIN3: MCU_PORT201.40, U102.32 (DTIN3/DTOUT3/PWM6/PTC3), U201.9 (D)
/GPT0: MCU_PORT201.49, U102.58 (GPT0/PWM1/PTA0)
/GPT1: MCU_PORT201.50, U102.59 (GPT1/PWM3/PTA1)
/GPT2: MCU_PORT201.51, U102.61 (GPT2PWM5//PTA2)
/GPT3: MCU_PORT201.52, U102.62 (GPT3/PWM7/PTA3)
/IRQ-1: MCU_PORT201.2, R118.1, U102.87 (~IRQ1/PNQ1/SYNCA/PWM1), U301.42 (O2)
/IRQ-2: MCU_PORT201.8, R119.1, U102.88 (~IRQ2/PNQ2), U301.43 (O1)
/IRQ-3: MCU_PORT201.31, R120.1, U102.89 (~IRQ3/PNQ3), U301.44 (O0)
/IRQ-4: MCU_PORT201.33, R121.1, SW201.1, U102.90 (~IRQ4/PNQ4)
/IRQ-5: MCU_PORT201.35, R122.1, SW202.1, U102.91 (~IRQ5/PNQ5)
/IRQ-6: MCU_PORT201.37, R123.1, U102.94 (~IRQ6/PNQ6)
/IRQ-7: D101.2 (A), MCU_PORT201.39, R124.1, U102.95 (~IRQ7/PNQ7)
/JTAG_EN: JP101.2, R111.2, U102.26 (JTAG_EN)
/PST0: BDM_PORT101.15, U102.65 (PST0/PDD0)
/PST1: BDM_PORT101.14, U102.66 (PST1/PDD1)
/PST2: BDM_PORT101.13, U102.69 (PST2/PDD2)
/PST3: BDM_PORT101.12, U102.70 (PST3/PDD3)
/PWM1: MCU_PORT201.13, U102.38 (PWM1/PTD0)
/PWM3: MCU_PORT201.15, U102.33 (PWM3/PTD1)
/PWM5: MCU_PORT201.30, U102.60 (PWM5/PTD2)
/PWM7: MCU_PORT201.32, U102.63 (PWM7/PTD3)
/QSPI_CLK: MCU_PORT201.21, PULUPEN201.1, U102.18 (QSPI_CLK/EZPCK/SCL/RTS1/PQS2), U301.48 (M11)
/QSPI_CS0: MCU_PORT201.23, PULUPEN201.3, U102.20 (QSPI_CS0/SDA/CTS1/PQS3)
/QSPI_CS1: MCU_PORT201.25, U102.19 (QSPI_CS1/PQS4), U301.54 (M1)
/QSPI_CS2: MCU_PORT201.27, U102.13 (QSPI_CS2/PQS5), U301.45 (M15)
/QSPI_CS3: MCU_PORT201.29, U102.12 (QSPI_CS3/SYNCA/SYNCB/PQS6)
/QSPI_DIN: MCU_PORT201.19, U102.16 (QSPI_DIN/EZPD/CANRX/RXD1/PQS1), U301.46 (M13)
/RCON-: MCU_PORT201.53, R112.1, U102.21 (RCON/EZPCS)
/RSTI-: BDM_PORT101.7, D102.2 (A), MCU_PORT201.6, R106.2, U102.96 (RSTI)
/RSTO-: MCU_PORT201.4, R115.1, U102.97 (RSTO)
/TCLK: BDM_PORT101.24 (P20), CLKOUT101.1, CT101.2, R114.2, R117.1
/UCTS0: MCU_PORT201.44, U102.6 (~UCTS0/CANRX/PUA3), UART_EN201.8
/UCTS1: MCU_PORT201.11, P302.1, U102.98 (~UCTS1/SYNCA/URXD2/PUB3), U301.49 (M4), UART_EN202.8
/UCTS2: MCU_PORT201.48, U102.27 (~UCTS2/PUC3), UART_EN203.8
/URTS0: MCU_PORT201.42, U102.9 (~URTS0/CANTX/PUA2), UART_EN201.6
/URTS1: MCU_PORT201.9, P302.3, U102.4 (~URTS1/SYNCB/UTXD2/PUB2), U301.53 (M2), UART_EN202.6
/URTS2: MCU_PORT201.46, U102.30 (~URTS2/PUC2), UART_EN203.6
/URXD0: MCU_PORT201.43, U102.7 (URXD0/PUA1), UART_EN201.4
/URXD1: MCU_PORT201.7, U102.100 (URXD1/PUB1), UART_EN202.4
/URXD2: MCU_PORT201.47, U102.28 (URXD2/PUC1), UART_EN203.4
/UTXD0: MCU_PORT201.41, U102.8 (UTXD0/PUA0), UART_EN201.2
/UTXD1: MCU_PORT201.5, U102.99 (UTXD1/PUB0), UART_EN202.2
/UTXD2: MCU_PORT201.45, U102.29 (UTXD2/PUC0), UART_EN203.2
/VCCA: C108.1, C109.1, L102.2, MCU_PORT201.55, MCU_PORT201.57, U102.49 (VRH), U102.50 (VCCA)
/VDDPLL: C102.1, C103.1, L101.2, U102.74 (VCCPLL)
/XTAL: C106.1, R125.1, U102.72 (XTAL), U301.128 (CLK0/IN0), Y101.2
/inout_user/CAN_H: CAN_TERM201.1, COM_SEL203.1, RCAN201.2, U205.7 (CAN+)
/inout_user/CAN_L: COM_SEL201.1, R209.1, RCAN202.2, U205.6 (CAN-)
/inout_user/CTS0: U202.8 (R2IN), UARTCAN201.7
/inout_user/CTS1: U203.8 (R2IN), UARTCAN202.7
/inout_user/CTS2/CANH: COM_SEL203.2 (PM), UARTCAN203.7
/inout_user/RTS0: U202.7 (T2OUT), UARTCAN201.8
/inout_user/RTS1: U203.7 (T2OUT), UARTCAN202.8
/inout_user/RTS2: U204.14 (T1OUT), UARTCAN203.8
/inout_user/RXD0: U202.13 (R1IN), UARTCAN201.3
/inout_user/RXD1: U203.13 (R1IN), UARTCAN202.3
/inout_user/RXD2: COM_SEL202.2 (PM), UARTCAN203.3
/inout_user/RxD_CAN: CAN_EN201.2, U205.4 (RxD)
/inout_user/TXD0: U202.14 (T1OUT), UARTCAN201.2
/inout_user/TXD1: U203.14 (T1OUT), UARTCAN202.2
/inout_user/TXD2/CANL: COM_SEL201.2 (PM), UARTCAN203.2
/inout_user/TxD_CAN: CAN_EN201.3, U205.1 (TxD)
/xilinx/+3,3V_OUT: P303.38, R302.2
/xilinx/LED_TEST1: R303.1, U301.28 (N15)
/xilinx/LED_TEST2: R304.1, U301.27 (N14)
/xilinx/TCK: P301.5, R301.2, U301.89 (E0/TCK)
/xilinx/TDI: P301.4, U301.4 (J0/TDI)
/xilinx/TDO: P301.6, U301.104 (A2/TDO)
/xilinx/TMS: P301.3, U301.20 (N0/TMS)
/xilinx/XIL_D0: P303.1, U301.12 (L2)
/xilinx/XIL_D1: P303.3, U301.11 (J15)
/xilinx/XIL_D2: P303.5, U301.7 (J4)
/xilinx/XIL_D3: P303.7, U301.8 (J11)
/xilinx/XIL_D4: P303.9, U301.2 (I0)
/xilinx/XIL_D5: P303.11, U301.143 (I4)
/xilinx/XIL_D6: P303.13, U301.140 (I14)
/xilinx/XIL_D7: P303.15, U301.138 (K2)
/xilinx/XIL_D8: P303.17, U301.136 (K11)
/xilinx/XIL_D9: P303.19, U301.131 (K15)
/xilinx/XIL_D10: P303.21, U301.122 (D15)
/xilinx/XIL_D11: P303.23, U301.119 (D11)
/xilinx/XIL_D12: P303.25, U301.114 (D0)
/xilinx/XIL_D13: P303.27, U301.111 (B12)
/xilinx/XIL_D14: P303.29, U301.109 (B4)
/xilinx/XIL_D15: P303.31, U301.108 (B1)
/xilinx/XIL_D16: P303.33, U301.100 (A12)
/xilinx/XIL_D17: P303.35, U301.101 (A11)
/xilinx/XIL_D18: P303.37, U301.97 (C1)
/xilinx/XIL_D19: P303.39, U301.96 (C2)
/xilinx/XIL_D20: P303.4, U301.6 (J3)
/xilinx/XIL_D21: P303.6, U301.10 (J14)
/xilinx/XIL_D22: P303.8, U301.5 (J2)
/xilinx/XIL_D23: P303.10, U301.1 (I1)
/xilinx/XIL_D24: P303.12, U301.142 (I12)
/xilinx/XIL_D25: P303.14, U301.139 (I15)
/xilinx/XIL_D26: P303.16, U301.137 (K4)
/xilinx/XIL_D27: P303.18, U301.134 (K12)
/xilinx/XIL_D28: P303.20, U301.132 (K14)
/xilinx/XIL_D29: P303.22, U301.117 (D2)
/xilinx/XIL_D30: P303.24, U301.118 (D4)
/xilinx/XIL_D31: P303.26, U301.116 (D1)
/xilinx/XIL_D32: P303.28, U301.98 (C0)
/xilinx/XIL_D33: P303.30, U301.112 (B14)
/xilinx/XIL_D34: P303.32, U301.113 (B15)
/xilinx/XIL_D35: P303.34, U301.107 (B0)
/xilinx/XIL_D36: P303.36, U301.99 (A13)
GND: BDM_PORT101.3, BDM_PORT101.5, BDM_PORT101.11, BDM_PORT101.20, BDM_PORT101.23, C101.1, C102.2, C103.2, C104.2, C105.2, C106.2, C107.2, C110.2, C111.2, C112.2, C113.2, C114.2, C115.2, C116.2, C117.2, C118.2, C119.2, C201.1, C202.2, C203.2, C207.2, C208.2, C212.2, C213.2, C214.2, C215.2, C216.2, C219.2, C221.2, C301.2, C302.2, C303.2, C304.2, C305.2, C306.2, C307.2, C308.2, C309.2, C310.2, C311.2, COM_SEL202.1, D201.2 (A), D301.1 (K), D302.1 (K), FB101.1, GND101.1, J201.1, J201.2, JP101.1, JP101.3, JP101.5, JP201.1, LED201.1 (K), LED202.1 (K), LED203.1 (K), LED204.1 (K), LED205.1 (K), LED_RST101.1 (K), LV101.3 (Gbd), MCU_PORT201.3, MCU_PORT201.54, MCU_PORT201.60, P301.2, P303.2, P303.40, R105.2, R113.2, R117.2, R205.1, R208.1, R210.2, R215.1, RCAN201.1, RST_SW101.2, SW201.2, SW202.2, TB201.2 (PM), U101.3 (GND), U102.3 (GND), U102.15 (GND), U102.24 (GND), U102.25 (GND), U102.35 (GND), U102.42 (GND), U102.56 (GND), U102.67 (GND), U102.71 (GNDPLL), U102.75 (GND), U102.82 (GND), U102.92 (GND), U201.7 (GND), U202.15 (GND), U203.15 (GND), U204.15 (GND), U205.2 (GND), U301.3 (GND), U301.13 (PORT_EN), U301.17 (GND), U301.33 (GND), U301.52 (GND), U301.57 (GND), U301.59 (GND), U301.64 (GND), U301.85 (GND), U301.105 (GND), U301.124 (GND), U301.125 (CLK3/IN3), U301.126 (CLK2/IN2), U301.127 (CLK1/IN1), U301.129 (GND), U301.135 (GND), UARTCAN201.5, UARTCAN202.5, UARTCAN203.5, VR201.3 (GND)
GNDA: C108.2, C109.2, FB101.2, MCU_PORT201.56, MCU_PORT201.58, U102.47 (VSSA), U102.48 (VRL)
unnamed: ABRT_SW101.1, R104.1
unnamed: BDM_PORT101.6, CT101.1
unnamed: BDM_PORT101.26 (P22), TA-101.1
unnamed: C104.1, R104.2, R105.1, U101.2
unnamed: CAN_TERM201.2, R209.2
unnamed: COM_SEL201.3, U204.7 (T2OUT)
unnamed: COM_SEL202.3, U204.8 (R2IN)
unnamed: COM_SEL203.3, U204.13 (R1IN)
unnamed: D101.1 (K), R103.2, U101.4
unnamed: C105.1, D102.1 (K), LV101.1 (Rst), RST_SW101.1
unnamed: C212.1, C213.1, D201.1 (K), F201.2, VR201.5 (IN)
unnamed: D301.2 (A), R303.2
unnamed: D302.2 (A), R304.2
unnamed: F201.1, SW_ONOFF201.2
unnamed: L102.1, VDDA101.2
unnamed: LED201.2 (A), R202.1
unnamed: LED202.2 (A), R203.1
unnamed: LED203.2 (A), R204.1
unnamed: LED204.2 (A), R206.1
unnamed: LED205.2 (A), R207.1
unnamed: LEDABRT101.1 (K), R103.1
unnamed: LED_RST101.2 (A), R116.2
unnamed: C201.2, MCU_PORT201.1, VX_EN201.2
unnamed: PULUPEN201.2, R211.2
unnamed: PULUPEN201.4, R212.2
unnamed: PULUPEN201.6, R213.2
unnamed: PULUPEN201.8, R214.2
unnamed: Q101.2 (B), R115.2
unnamed: Q101.3 (C), R116.1
unnamed: J201.3, SW_ONOFF201.3, TB201.1
unnamed: R114.1, U102.64 (TCLK/PSTCLK/CLKOUT)
unnamed: R113.1, U102.5 (TEST)
unnamed: JP201.2, R201.2, U201.1 (E), U201.4 (E), U201.10 (E), U201.13 (E)
unnamed: R202.2, U201.3 (O)
unnamed: R203.2, U201.6 (O)
unnamed: R206.2, U201.8 (O)
unnamed: R204.2, U201.11 (O)
unnamed: C205.1, U202.1 (C1+)
unnamed: C205.2, U202.3 (C1-)
unnamed: C206.1, U202.4 (C2+)
unnamed: C206.2, U202.5 (C2-)
unnamed: U202.12 (R1OUT), UART_EN201.3
unnamed: U202.9 (R2OUT), UART_EN201.7
unnamed: U202.11 (T1IN), UART_EN201.1
unnamed: R205.2, U202.10 (T2IN), UART_EN201.5
unnamed: C204.2, U202.2 (V+)
unnamed: C207.1, U202.6 (V-)
unnamed: C210.1, U203.1 (C1+)
unnamed: C210.2, U203.3 (C1-)
unnamed: C211.1, U203.4 (C2+)
unnamed: C211.2, U203.5 (C2-)
unnamed: U203.12 (R1OUT), UART_EN202.3
unnamed: U203.9 (R2OUT), UART_EN202.7
unnamed: U203.11 (T1IN), UART_EN202.1
unnamed: R208.2, U203.10 (T2IN), UART_EN202.5
unnamed: C209.2, U203.2 (V+)
unnamed: C214.1, U203.6 (V-)
unnamed: C218.1, U204.1 (C1+)
unnamed: C218.2, U204.3 (C1-)
unnamed: C220.1, U204.4 (C2+)
unnamed: C220.2, U204.5 (C2-)
unnamed: U204.12 (R1OUT), UART_EN203.7
unnamed: U204.9 (R2OUT), UART_EN203.3
unnamed: R215.2, U204.11 (T1IN), UART_EN203.5
unnamed: U204.10 (T2IN), UART_EN203.1
unnamed: C217.2, U204.2 (V+)
unnamed: C221.1, U204.6 (V-)
unnamed: R210.1, RS201.1, U205.8 (Rsl)
unnamed: U205.5 (Vref), VREF201.1
unnamed: P302.4, U301.31 (P4)
unnamed: P302.2, U301.32 (P11)
unnamed: UARTCAN201.1, UARTCAN201.4, UARTCAN201.6
unnamed: UARTCAN202.1, UARTCAN202.4, UARTCAN202.6
unnamed: UARTCAN203.1, UARTCAN203.4, UARTCAN203.6
